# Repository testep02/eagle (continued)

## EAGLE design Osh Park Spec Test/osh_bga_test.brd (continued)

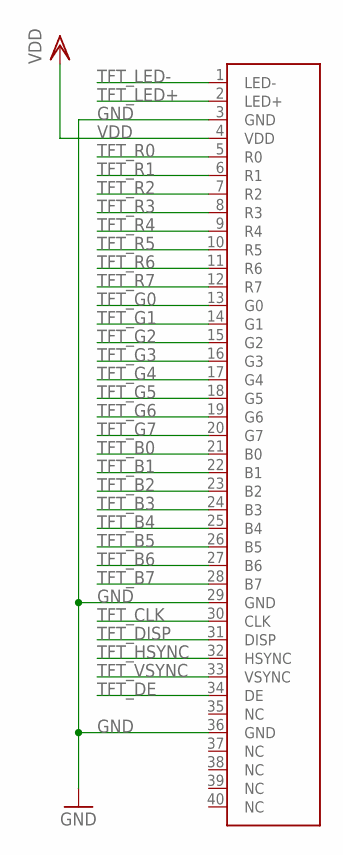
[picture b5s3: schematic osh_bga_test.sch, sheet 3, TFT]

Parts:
CON1: NH-4.3; FPC-40

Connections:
GND: CON1.3 (GND), CON1.29 (GND), CON1.36 (GND); also elsewhere on the board
TFT_B0: CON1.21 (B0); also elsewhere on the board
TFT_B1: CON1.22 (B1); also elsewhere on the board
TFT_B2: CON1.23 (B2); also elsewhere on the board
TFT_B3: CON1.24 (B3); also elsewhere on the board
TFT_B4: CON1.25 (B4); also elsewhere on the board
TFT_B5: CON1.26 (B5); also elsewhere on the board
TFT_B6: CON1.27 (B6); also elsewhere on the board
TFT_B7: CON1.28 (B7); also elsewhere on the board
TFT_CLK: CON1.30 (CLK); also elsewhere on the board
TFT_DE: CON1.34 (DE); also elsewhere on the board
TFT_DISP: CON1.31 (DISP)
TFT_G0: CON1.13 (G0); also elsewhere on the board
TFT_G1: CON1.14 (G1); also elsewhere on the board
TFT_G2: CON1.15 (G2); also elsewhere on the board
TFT_G3: CON1.16 (G3); also elsewhere on the board
TFT_G4: CON1.17 (G4); also elsewhere on the board
TFT_G5: CON1.18 (G5); also elsewhere on the board
TFT_G6: CON1.19 (G6); also elsewhere on the board
TFT_G7: CON1.20 (G7); also elsewhere on the board
TFT_HSYNC: CON1.32 (HSYNC); also elsewhere on the board
TFT_LED+: CON1.2 (LED+)
TFT_LED-: CON1.1 (LED-)
TFT_R0: CON1.5 (R0); also elsewhere on the board
TFT_R1: CON1.6 (R1); also elsewhere on the board
TFT_R2: CON1.7 (R2); also elsewhere on the board
TFT_R3: CON1.8 (R3); also elsewhere on the board
TFT_R4: CON1.9 (R4); also elsewhere on the board
TFT_R5: CON1.10 (R5); also elsewhere on the board
TFT_R6: CON1.11 (R6); also elsewhere on the board
TFT_R7: CON1.12 (R7); also elsewhere on the board
TFT_VSYNC: CON1.33 (VSYNC); also elsewhere on the board
VDD: CON1.4 (VDD); also elsewhere on the board

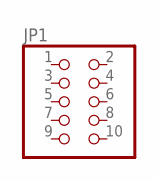
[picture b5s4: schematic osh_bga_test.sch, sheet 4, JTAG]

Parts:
JP1: PINHD-2X5; 2X05

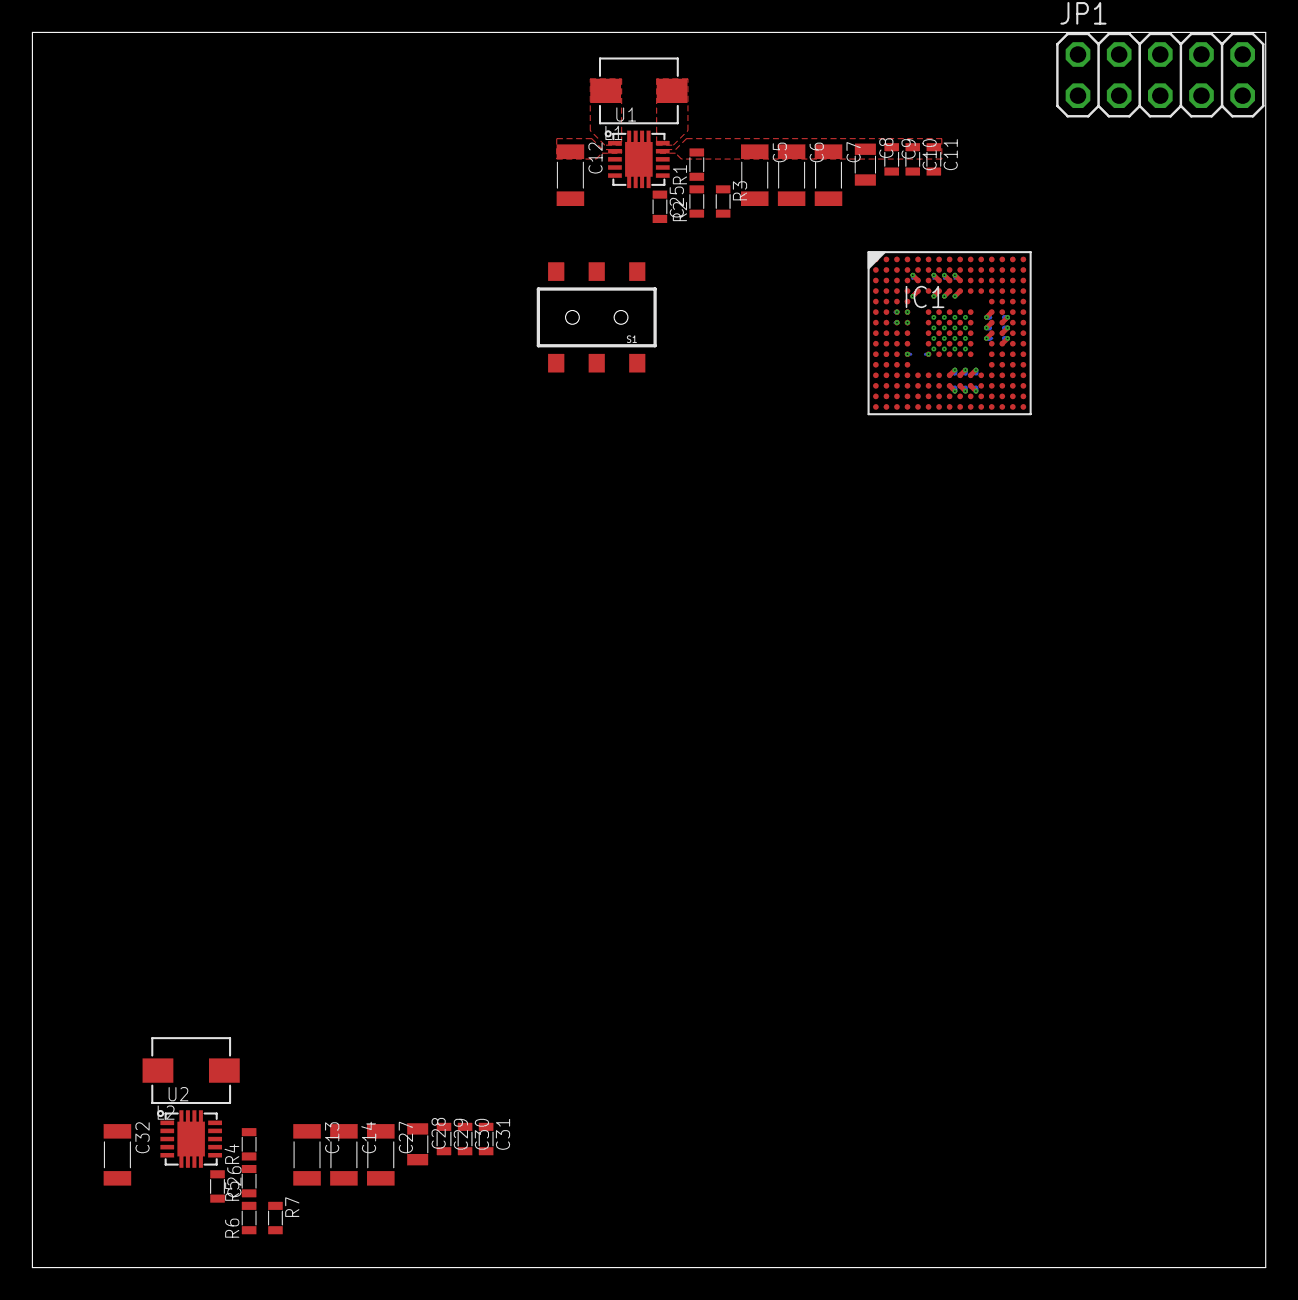
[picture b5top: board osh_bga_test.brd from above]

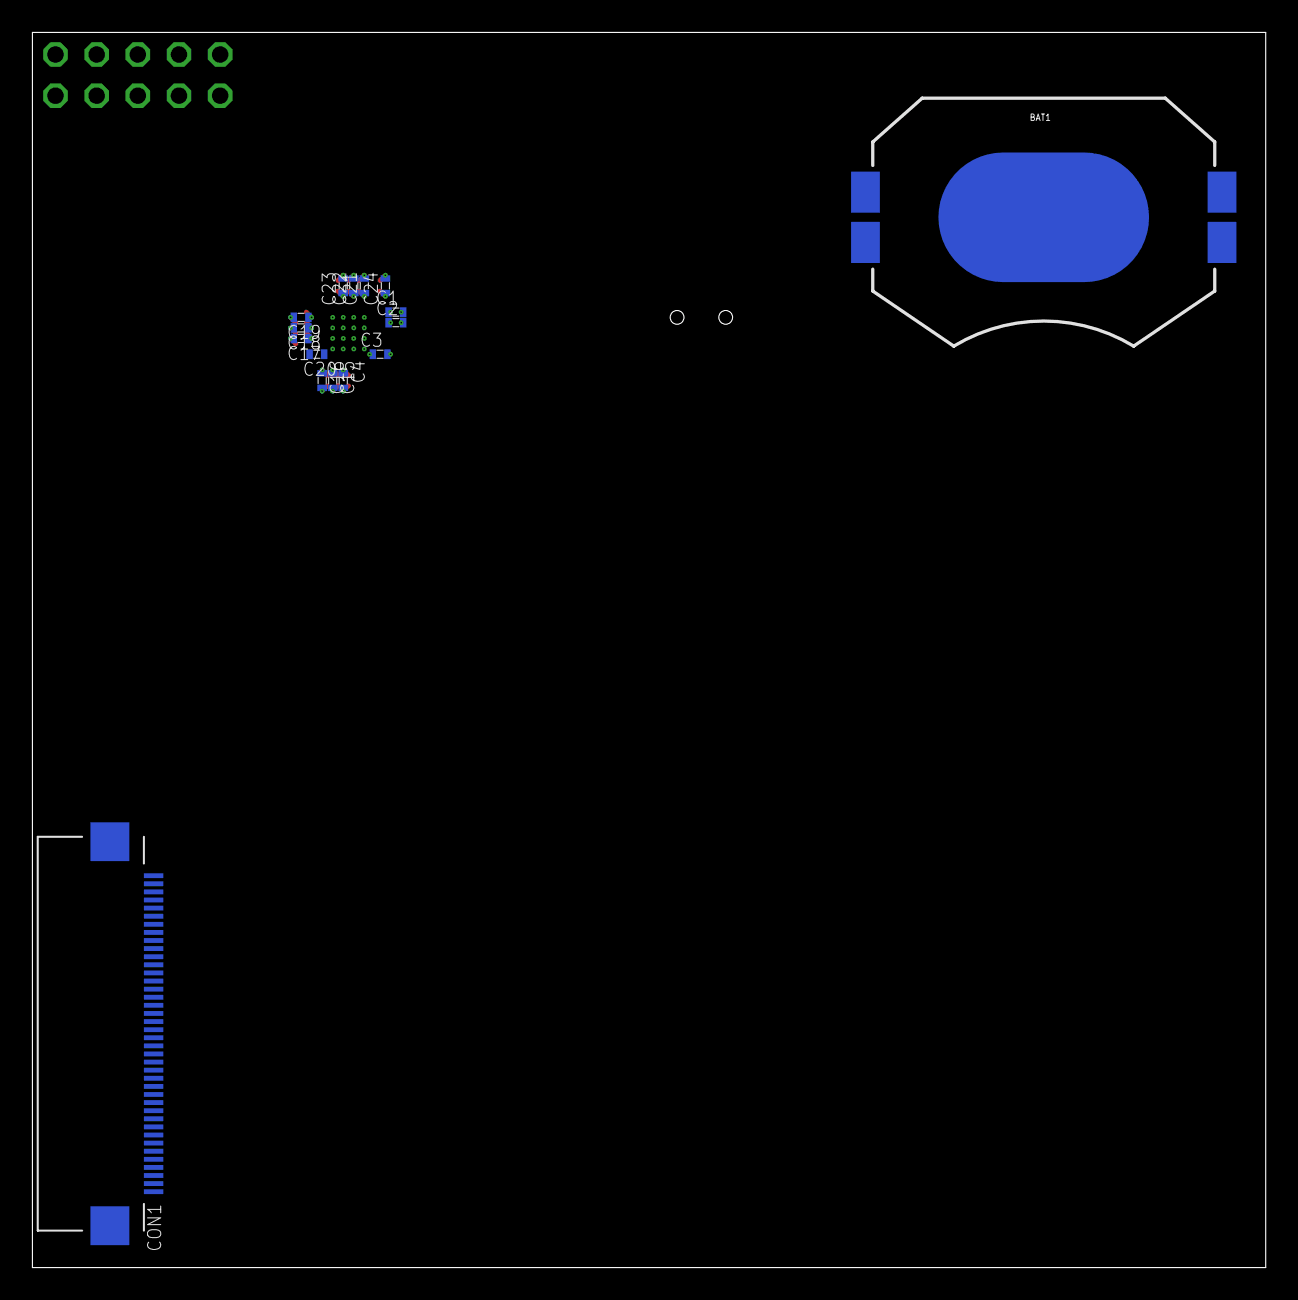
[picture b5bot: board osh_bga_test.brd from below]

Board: 4 copper layers, 76.1 x 76.2 mm, 48 parts (16 on the bottom side), 46 nets.

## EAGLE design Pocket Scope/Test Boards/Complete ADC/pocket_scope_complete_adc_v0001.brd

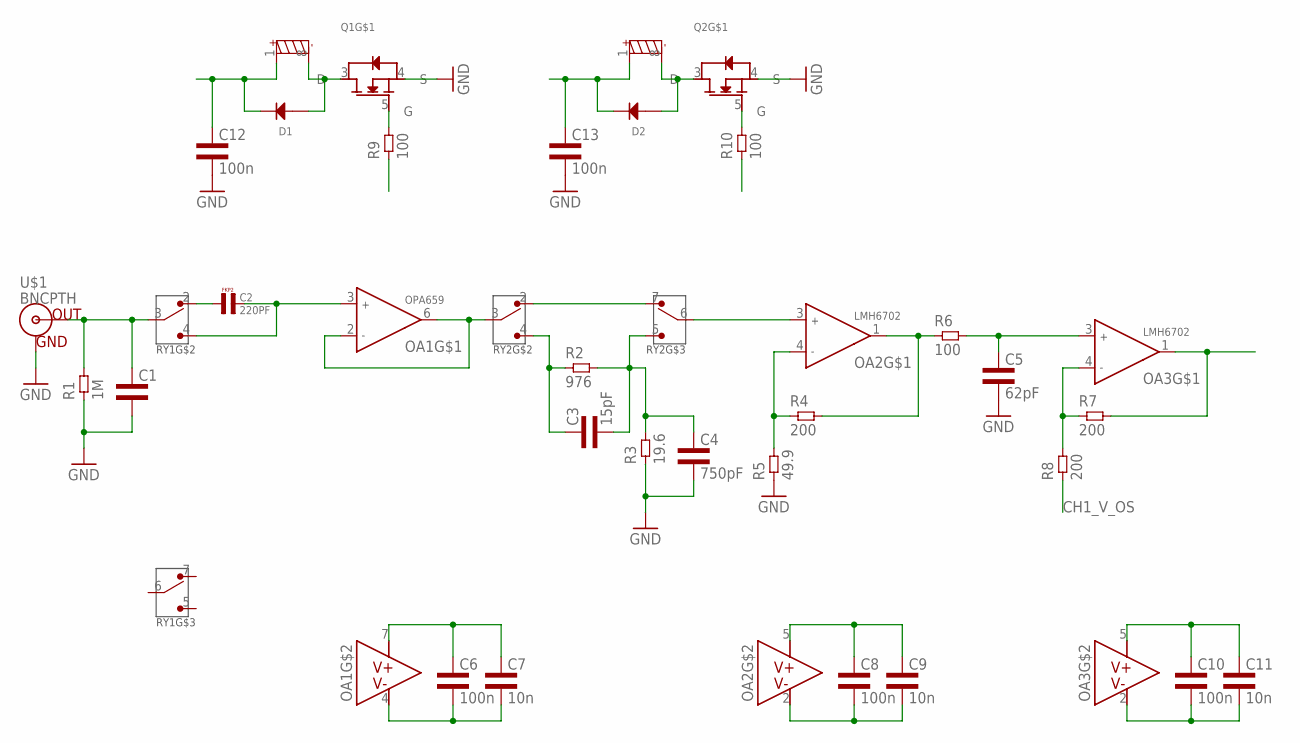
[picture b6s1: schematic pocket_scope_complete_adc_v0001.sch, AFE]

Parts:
C1: CAP0603L3; 0603L3
C2: 220PF; R5B4K5
C3: 15pF; 0603L3
C4: 750pF; 0603L3
C5: 62pF; 0603L3
C6, C8, C10, C12, C13: 100n; 0603L3
C7, C9, C11: 10n; 0603L3
D1, D2: DIODESMA; SMA-2
OA1: OPA659; S-PVSON-N8
OA2, OA3: LMH6702; R-PDSO-G5
Q1, Q2: 2N7002DWA; SC70
R1: 1M; 0603L3
R2: 976; 0603L3
R3: 19.6; 0603L3
R4, R7, R8: 200; 0603L3
R5: 49.9; 0603L3
R6, R9, R10: 100; 0603L3
RY1, RY2: RELAY_SMD; G6J-2FL-Y
U$1: BNCPTH; BNC

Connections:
1_TO_1: RY2.2 (T1), RY2.7 (T1)
10_TO_1_IN: C3.P$1 (1), R2.P$1 (1), RY2.4 (T2)
10_TO_1_OUT: C3.P$2 (2), C4.P$1 (1), R2.P$2 (2), R3.P$2 (2), RY2.5 (T2)
AN_CH1: OA3.1 (OUTA), R7.P$2 (2)
CH1_IN: C1.P$1 (1), R1.P$2 (2), RY1.3 (D), U$1.S (OUT)
CH1_V_OS: R8.P$1 (1)
GND: C1.P$2 (2), C4.P$2 (2), C5.P$2 (2), C12.P$2 (2), C13.P$2 (2), Q1.4 (S), Q2.4 (S), R1.P$1 (1), R3.P$1 (1), R5.P$1 (1), U$1.GND
unnamed: D1.1 (ANODE), Q1.3 (D), RY1.8 (COIL_-)
unnamed: C13.P$1 (1), D2.2 (CATHODE), RY2.1 (COIL_+)
unnamed: C2.1, RY1.2 (T1)
unnamed: Q1.5 (G), R9.P$2 (2)
unnamed: D2.1 (ANODE), Q2.3 (D), RY2.8 (COIL_-)
unnamed: Q2.5 (G), R10.P$2 (2)
unnamed: C12.P$1 (1), D1.2 (CATHODE), RY1.1 (COIL_+)
unnamed: OA2.3 (INA+), RY2.6 (D)
unnamed: OA2.1 (OUTA), R4.P$2 (2), R6.P$1 (1)
unnamed: C6.P$1 (1), C7.P$1 (1), OA1.7 (V+)
unnamed: C6.P$2 (2), C7.P$2 (2), OA1.4 (V-)
unnamed: C8.P$2 (2), C9.P$2 (2), OA2.2 (V-)
unnamed: C8.P$1 (1), C9.P$1 (1), OA2.5 (V+)
unnamed: C10.P$1 (1), C11.P$1 (1), OA3.5 (V+)
unnamed: C10.P$2 (2), C11.P$2 (2), OA3.2 (V-)
OA1_IN: C2.2, OA1.3 (INA+), RY1.4 (T2)
OA1_OUT: OA1.2 (INA-), OA1.6 (OUTA), RY2.3 (D)
OA2_FB: OA2.4 (INA-), R4.P$1 (1), R5.P$2 (2)
OA3_FB: OA3.4 (INA-), R7.P$1 (1), R8.P$2 (2)
OA3_IN: C5.P$1 (1), OA3.3 (INA+), R6.P$2 (2)

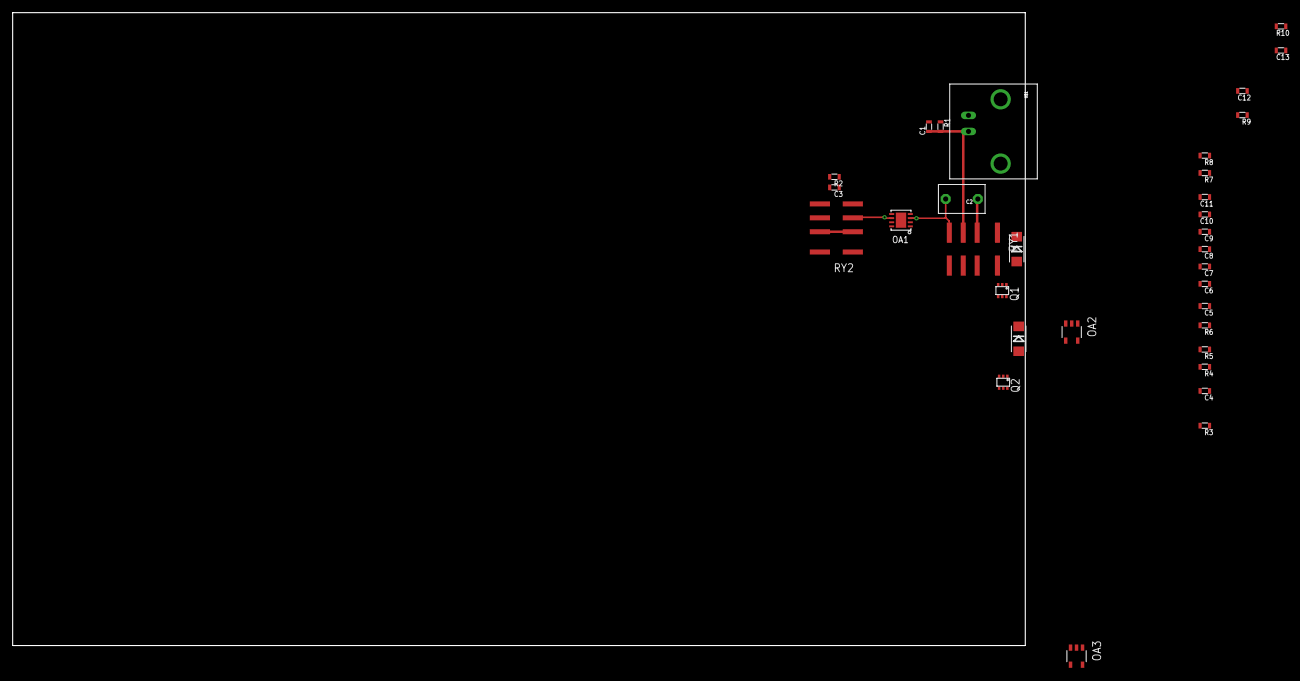
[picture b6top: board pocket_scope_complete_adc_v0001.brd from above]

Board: 2 copper layers, 160.0 x 100.0 mm, 33 parts (0 on the bottom side), 26 nets.
